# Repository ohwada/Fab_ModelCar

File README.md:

Fab_ModelCar
===============

Model Car <br>
* the parts are made with laser cutter and milling machine.
* controlled by Bluetooth form Android phone.

### Car1
Body: frame-geared-motor-1.ai <br>
Motor: yellow geared motor <br>

Electronic board: moter_shield_1 <br>
* Motor driver: TA7291P
* Bluetooth: Microchip RN-42
* with Arduino Uno

Arduino sketch: rn42_motor_1 <br>
Android program (App Inventor): BT_Car_1.aia <br>

### Car2
Body: frame-tamiya-1.ai <br>
Motor: Tamiya double gearbox kit <br>

Electronic board: arduino_motor_1 <br>
* CPU: ATMEGA328P (Arduino Uno compatible)
* Motor driver: TA7291P
* Bluetooth: Microchip RN-42

Arduino sketch: rn42_motor_1 <br>
Android program (App Inventor): BT_Car_1.aia <br>

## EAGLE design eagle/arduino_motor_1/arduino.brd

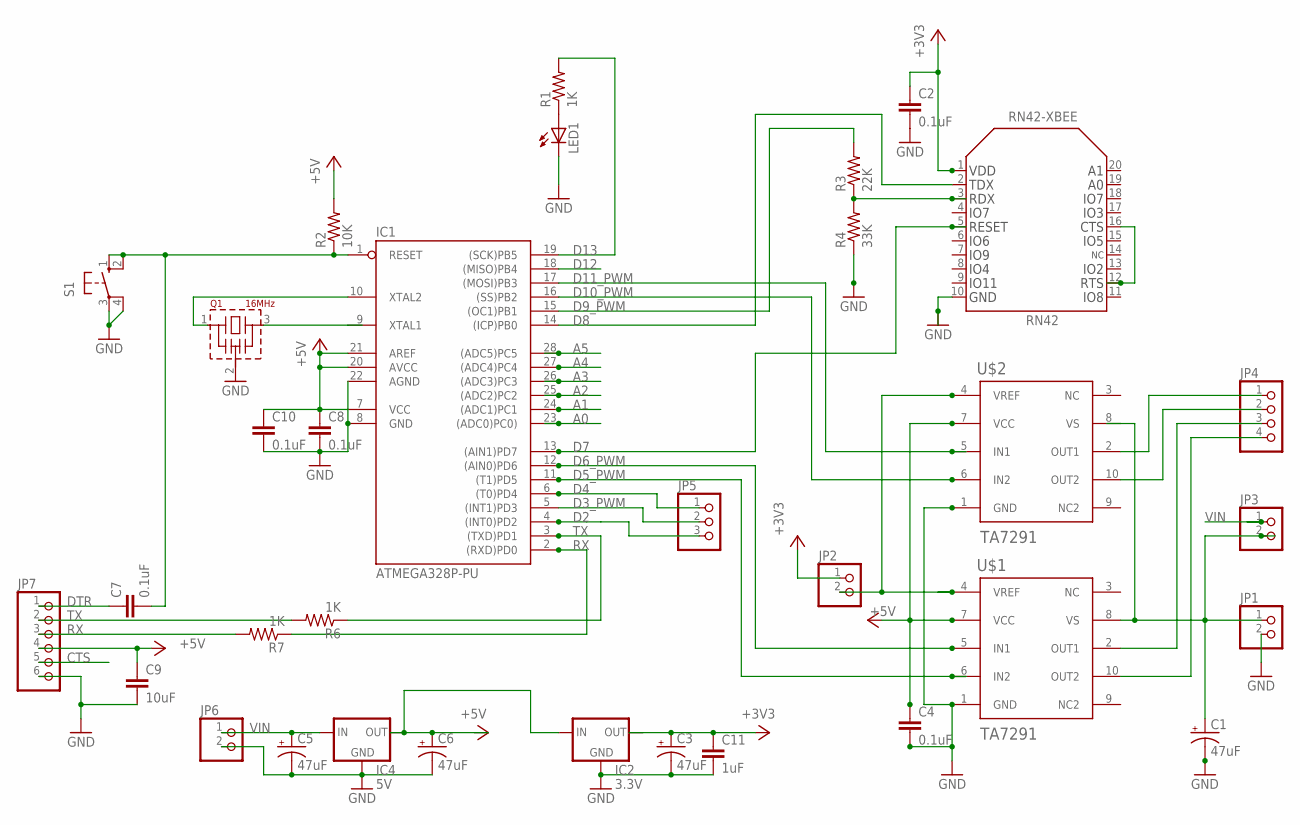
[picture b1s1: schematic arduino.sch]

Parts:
C1, C3, C5, C6: 47uF; E2-5
C2, C4, C7, C8, C10: 0.1uF; C050-025X075
C9: 10uF; C050-025X075
C11: 1uF; C050-025X075
IC1: ATMEGA328P-PU; DIL28-3
IC2: 3.3V; 78XXS
IC4: 5V; 78XXS
JP1, JP2, JP3, JP6: PINHD-1X2; 1X02
JP4: PINHD-1X4; 1X04
JP5: PINHD-1X3; 1X03
JP7: PINHD-1X6; 1X06
LED1: LED3MM
Q1: 16MHz; CSTLS_G8
R1, R6, R7: 1K; 0207/10
R2: 10K; 0207/10
R3: 22K; 0207/10
R4: 33K; 0207/10
S1: 10-XX; B3F-10XX
U$1, U$2: TA7291; HSIP10
U$3: RN42-XBEE; RN42-XBEE-PKG

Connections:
+3V3: C2.1, C3.+, C11.1, IC2.OUT, JP2.1, U$3.1
+5V: C4.1, C6.+, C8.1, C9.1, C10.1, IC1.7 (VCC), IC1.20 (AVCC), IC1.21 (AREF), IC2.IN, IC4.OUT, JP7.4, R2.2, U$1.7 (VCC), U$2.7 (VCC)
A0: IC1.23 ((ADC0)PC0))
A1: IC1.24 ((ADC1)PC1)
A2: IC1.25 ((ADC2)PC2)
A3: IC1.26 ((ADC3)PC3)
A4: IC1.27 ((ADC4)PC4)
A5: IC1.28 ((ADC5)PC5)
CTS: JP7.5
D2: IC1.4 ((INT0)PD2), JP5.3
D3_PWM: IC1.5 ((INT1)PD3), JP5.2
D4: IC1.6 ((T0)PD4), JP5.1
D5_PWM: IC1.11 ((T1)PD5), U$1.6 (IN2)
D6_PWM: IC1.12 ((AIN0)PD6), U$1.5 (IN1)
D7: IC1.13 ((AIN1)PD7), U$3.5
D8: IC1.14 ((ICP)PB0), U$3.2
D9_PWM: IC1.15 ((OC1)PB1), R3.2
D10_PWM: IC1.16 ((SS)PB2), U$2.6 (IN2)
D11_PWM: IC1.17 ((MOSI)PB3), U$2.5 (IN1)
D12: IC1.18 ((MISO)PB4)
D13: IC1.19 ((SCK)PB5), R1.2
DTR: C7.1, JP7.1
GND: C1.-, C2.2, C3.-, C4.2, C5.-, C6.-, C8.2, C9.2, C10.2, C11.2, IC1.8 (GND), IC1.22 (AGND), IC2.GND, IC4.GND, JP1.2, JP6.2, JP7.6, LED1.K (C), Q1.2 (VSS), R4.1, S1.3, S1.4 (P1), U$1.1 (GND), U$2.1 (GND), U$3.10
unnamed: R3.1, R4.2, U$3.3
unnamed: JP2.2, U$1.4 (VREF), U$2.4 (VREF)
unnamed: U$3.12, U$3.16
unnamed: LED1.A, R1.1
unnamed: IC1.9 (XTAL1), Q1.3
unnamed: IC1.10 (XTAL2), Q1.1
unnamed: JP4.4, U$1.10 (OUT2)
unnamed: JP7.2, R6.2
unnamed: JP7.3, R7.2
unnamed: JP4.1, U$2.2 (OUT1)
unnamed: JP4.2, U$2.10 (OUT2)
unnamed: JP4.3, U$1.2 (OUT1)
RESET: C7.2, IC1.1 (RESET), R2.1, S1.1 (S), S1.2 (S1)
RX: IC1.2 ((RXD)PD0), R7.1
TX: IC1.3 ((TXD)PD1), R6.1
VIN: C5.+, IC4.IN, JP3.1, JP6.1
VS: C1.+, JP1.1, JP3.2, U$1.8 (VS), U$2.8 (VS)

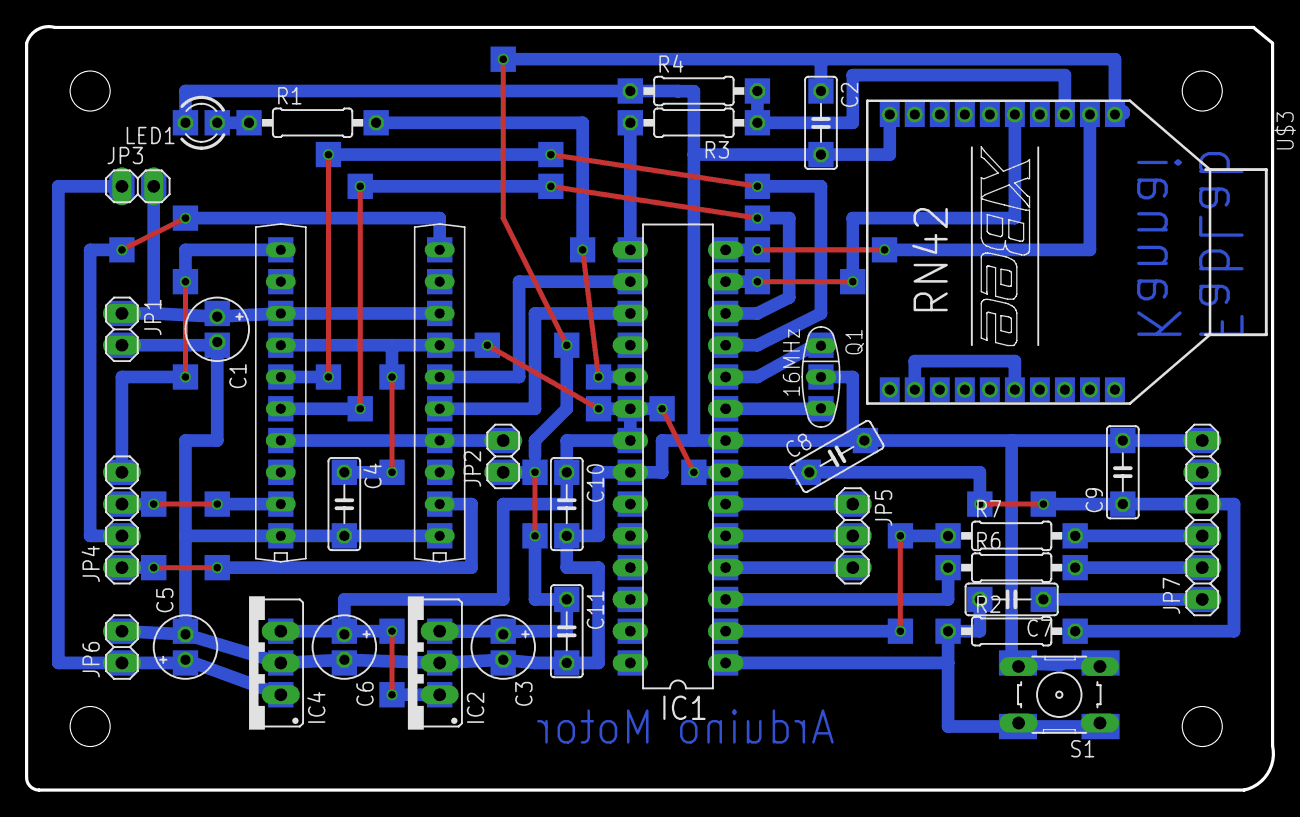
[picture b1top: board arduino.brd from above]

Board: 2 copper layers, 99.7 x 61.0 mm, 33 parts (0 on the bottom side), 32 nets.

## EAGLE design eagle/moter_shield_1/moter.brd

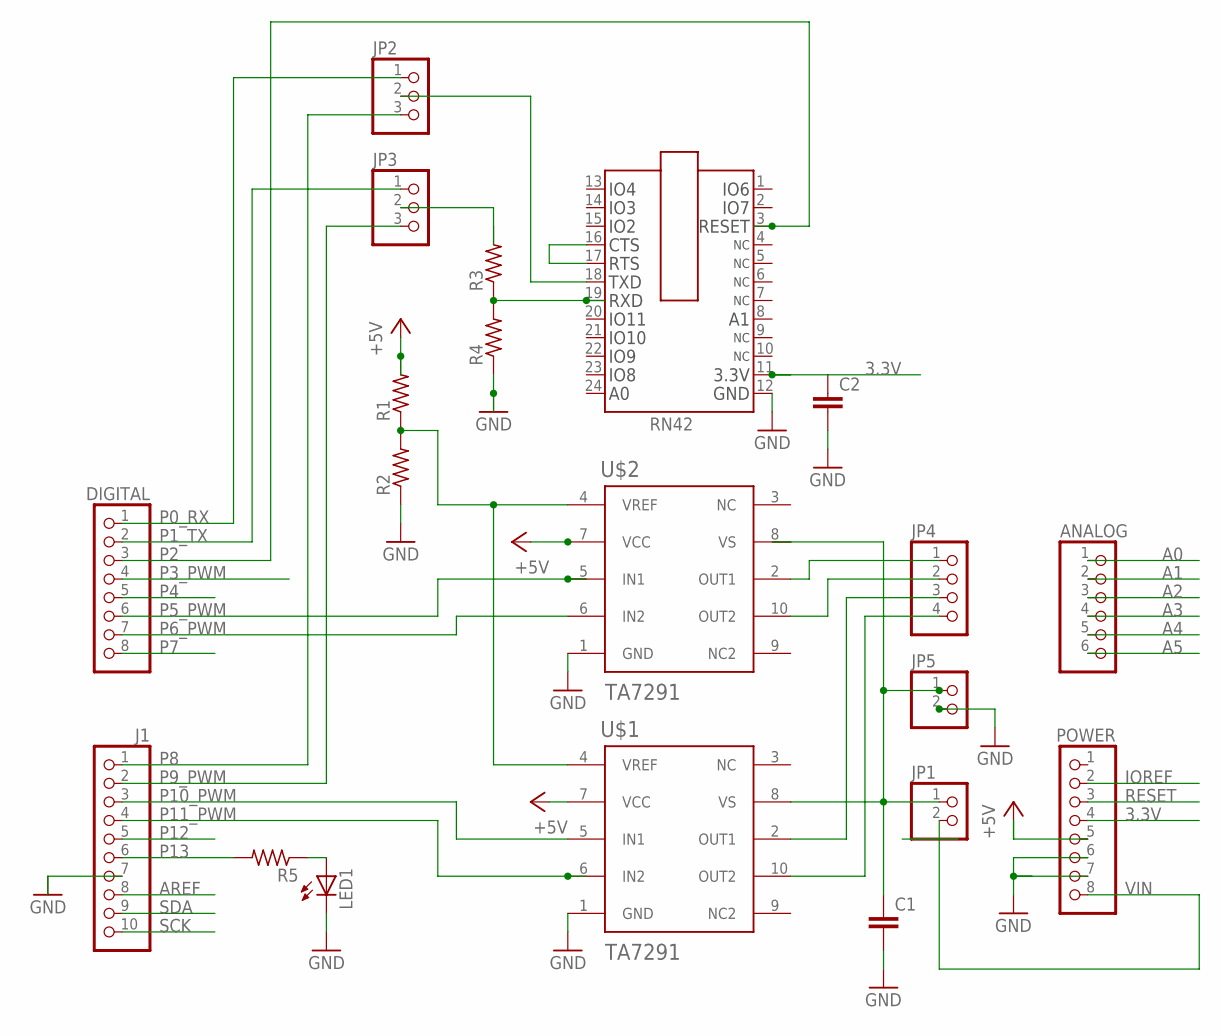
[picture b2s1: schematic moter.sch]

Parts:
ANALOG: PINHD-1X6; 1X06
C1, C2: C-EU050-025X075; C050-025X075
DIGITAL: PINHD-1X8TH; 1X08-TH
IC1: RN42-9; RN42-PKG
J1: PINHD-1X10TH; 1X10-TH
JP1, JP5: PINHD-1X2; 1X02
JP2, JP3: PINHD-1X3; 1X03
JP4: PINHD-1X4; 1X04
LED1: LED3MM
POWER: PINHD-1X8TH; 1X08-TH
R1, R2, R3, R4, R5: R-US_0207/10; 0207/10
U$1, U$2: TA7291; HSIP10

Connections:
3.3V: C2.1, IC1.11, POWER.4
+5V: POWER.5, R1.2, U$1.7 (VCC), U$2.7 (VCC)
A0: ANALOG.1
A1: ANALOG.2
A2: ANALOG.3
A3: ANALOG.4
A4: ANALOG.5
A5: ANALOG.6
AREF: J1.8
GND: C1.2, C2.2, IC1.12, J1.7, JP5.2, LED1.K (C), POWER.6, POWER.7, R2.1, R4.1, U$1.1 (GND), U$2.1 (GND)
IOREF: POWER.2
unnamed: JP4.3, U$1.2 (OUT1)
unnamed: LED1.A, R5.1
unnamed: IC1.16, IC1.17
unnamed: JP3.2, R3.2
unnamed: IC1.18, JP2.2
unnamed: IC1.19, R3.1, R4.2
unnamed: R1.1, R2.2, U$1.4 (VREF), U$2.4 (VREF)
unnamed: JP4.4, U$1.10 (OUT2)
unnamed: JP4.2, U$2.10 (OUT2)
unnamed: JP4.1, U$2.2 (OUT1)
P0_RX: DIGITAL.1, JP2.1
P1_TX: DIGITAL.2, JP3.1
P2: DIGITAL.3, IC1.3
P3_PWM: DIGITAL.4
P4: DIGITAL.5
P5_PWM: DIGITAL.6, U$2.5 (IN1)
P6_PWM: DIGITAL.7, U$2.6 (IN2)
P7: DIGITAL.8
P8: J1.1, JP2.3
P9_PWM: J1.2, JP3.3
P10_PWM: J1.3, U$1.5 (IN1)
P11_PWM: J1.4, U$1.6 (IN2)
P12: J1.5
P13: J1.6, R5.2
RESET: POWER.3
SCK: J1.10
SDA: J1.9
VIN: JP1.2, POWER.8
VS: C1.1, JP1.1, JP5.1, U$1.8 (VS), U$2.8 (VS)

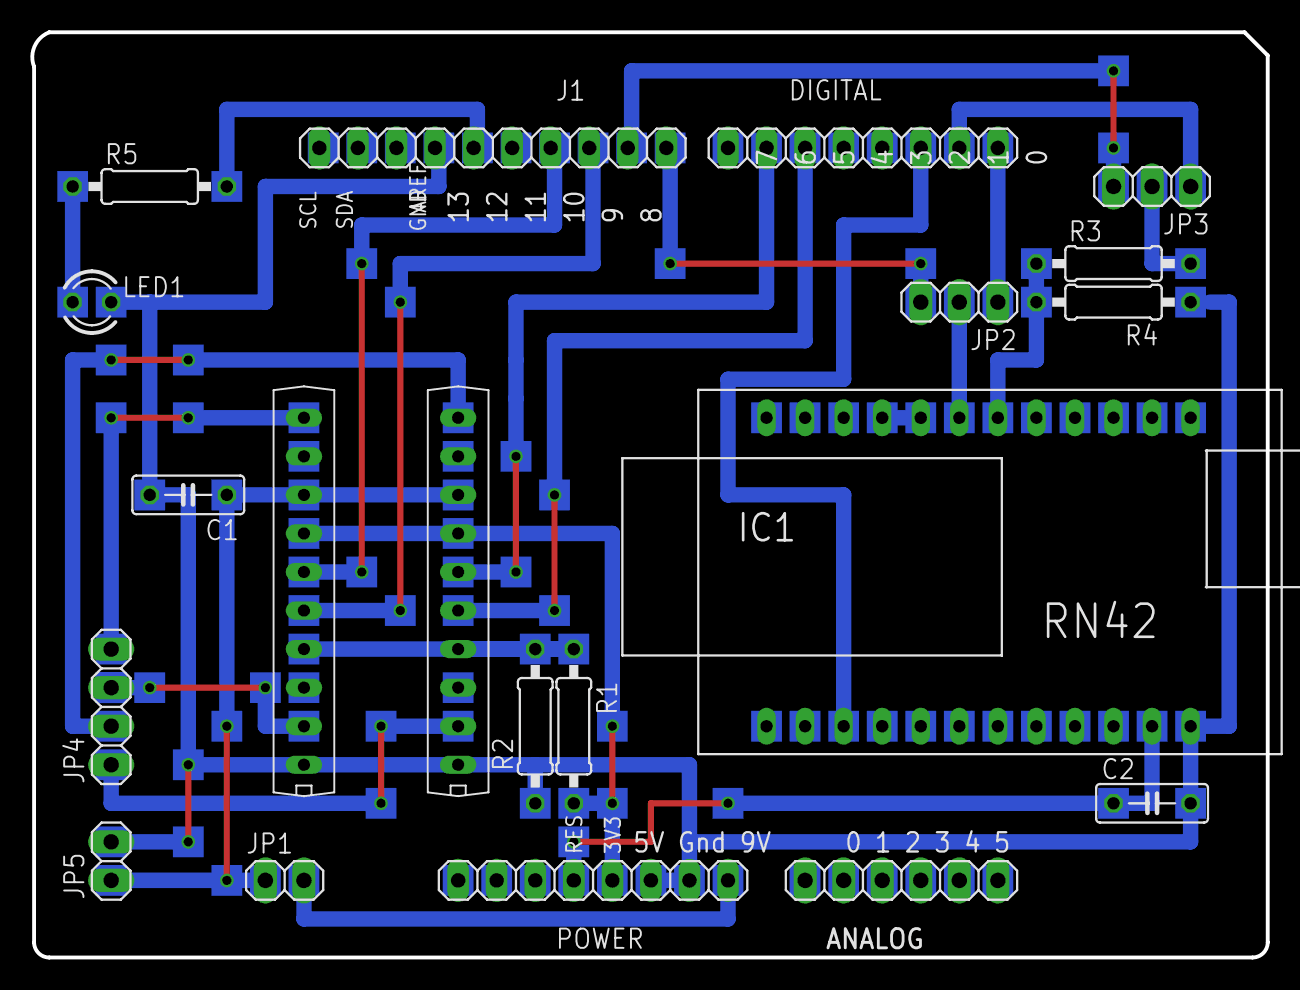
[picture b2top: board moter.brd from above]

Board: 2 copper layers, 81.4 x 61.0 mm, 20 parts (0 on the bottom side), 25 nets.

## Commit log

2015-07-30 First Version
2015-07-31 app inventor
2015-07-31 car1
